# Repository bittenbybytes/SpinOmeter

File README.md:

# SpinOmeter
Spin gauge module for ultimate discs

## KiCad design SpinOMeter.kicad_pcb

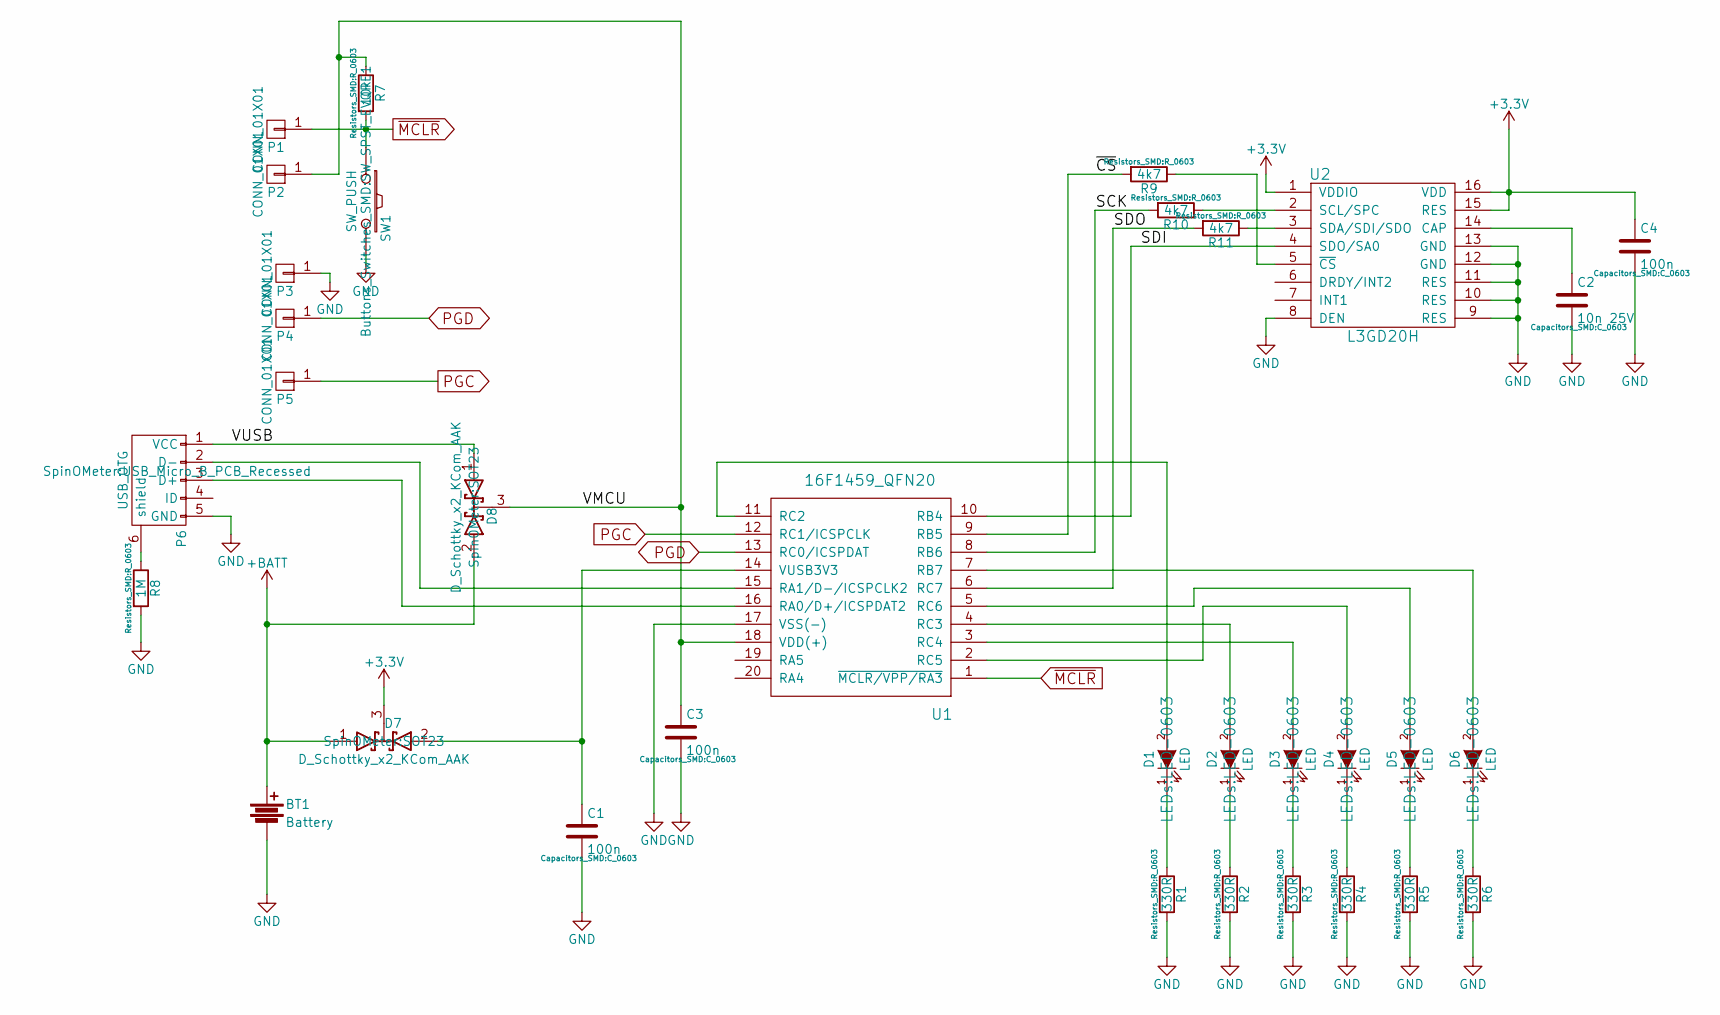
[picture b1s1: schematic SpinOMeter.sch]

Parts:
BT1: Battery; CR2032_Holder_THT
C1, C3, C4: 100n; C_0603
C2: 10n 25V; C_0603
D1, D2, D3, D4, D5, D6: LED; LED-0603
D7, D8: D_Schottky_x2_KCom_AAK; SOT23
P1, P2, P3, P4, P5: CONN_01X01; PINTST
P6: USB_OTG; USB_Micro_B_PCB_Recessed
R1, R2, R3, R4, R5, R6: 330R; R_0603
R7: 10k; R_0603
R8: 1M; R_0603
R9, R10, R11: 4k7; R_0603
SW1: SW_PUSH; SW_SPST_EVQPE1
U1: 16F1459_QFN20; QFN20_0.5mm_pitch
U2: L3GD20H; LGA16_3x3x1

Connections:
+3V3: C4.1, D7.3 (K), U2.1 (VDDIO), U2.15 (RES), U2.16 (VDD)
+BATT: BT1.1, D7.1 (A), D8.2 (A)
/SCK: R10.2, U1.8 (RB6)
/SDI: U1.10 (RB4), U2.4 (SDO/SA0)
/SDO: R11.2, U1.6 (RC7)
/VMCU: C3.1, D8.3 (K), P2.1, R7.1, U1.18 (VDD(+))
/VUSB: D8.1 (A), P6.1 (VCC)
/~CS~: R9.2, U1.9 (RB5)
GND: BT1.2, C1.2, C2.2, C3.2, C4.2, P3.1, P6.5 (GND), R1.2, R2.2, R3.2, R4.2, R5.2, R6.2, R8.2, SW1.2, U1.17 (VSS(-)), U2.8 (DEN), U2.9 (RES), U2.10 (RES), U2.11 (RES), U2.12 (GND), U2.13 (GND)
unnamed: C1.1, D7.2 (A), U1.14 (VUSB3V3)
unnamed: C2.1, U2.14 (CAP)
unnamed: D1.1 (K), R1.1
unnamed: D1.2 (A), U1.11 (RC2)
unnamed: D2.1 (K), R2.1
unnamed: D2.2 (A), U1.4 (RC3)
unnamed: D3.1 (K), R3.1
unnamed: D3.2 (A), U1.3 (RC4)
unnamed: D4.1 (K), R4.1
unnamed: D4.2 (A), U1.2 (RC5)
unnamed: D5.1 (K), R5.1
unnamed: D5.2 (A), U1.5 (RC6)
unnamed: D6.1 (K), R6.1
unnamed: D6.2 (A), U1.7 (RB7)
unnamed: P6.2 (D-), U1.15 (RA1/D-/ICSPCLK2)
unnamed: P6.3 (D+), U1.16 (RA0/D+/ICSPDAT2)
unnamed: P6.6 (shield), R8.1
unnamed: R9.1, U2.5 (~CS~)
unnamed: R10.1, U2.2 (SCL/SPC)
unnamed: R11.1, U2.3 (SDA/SDI/SDO)
PGC: P5.1, U1.12 (RC1/ICSPCLK)
PGD: P4.1, U1.13 (RC0/ICSPDAT)
~MCLR: P1.1, R7.2, SW1.1, U1.1 (~MCLR/VPP/RA3)

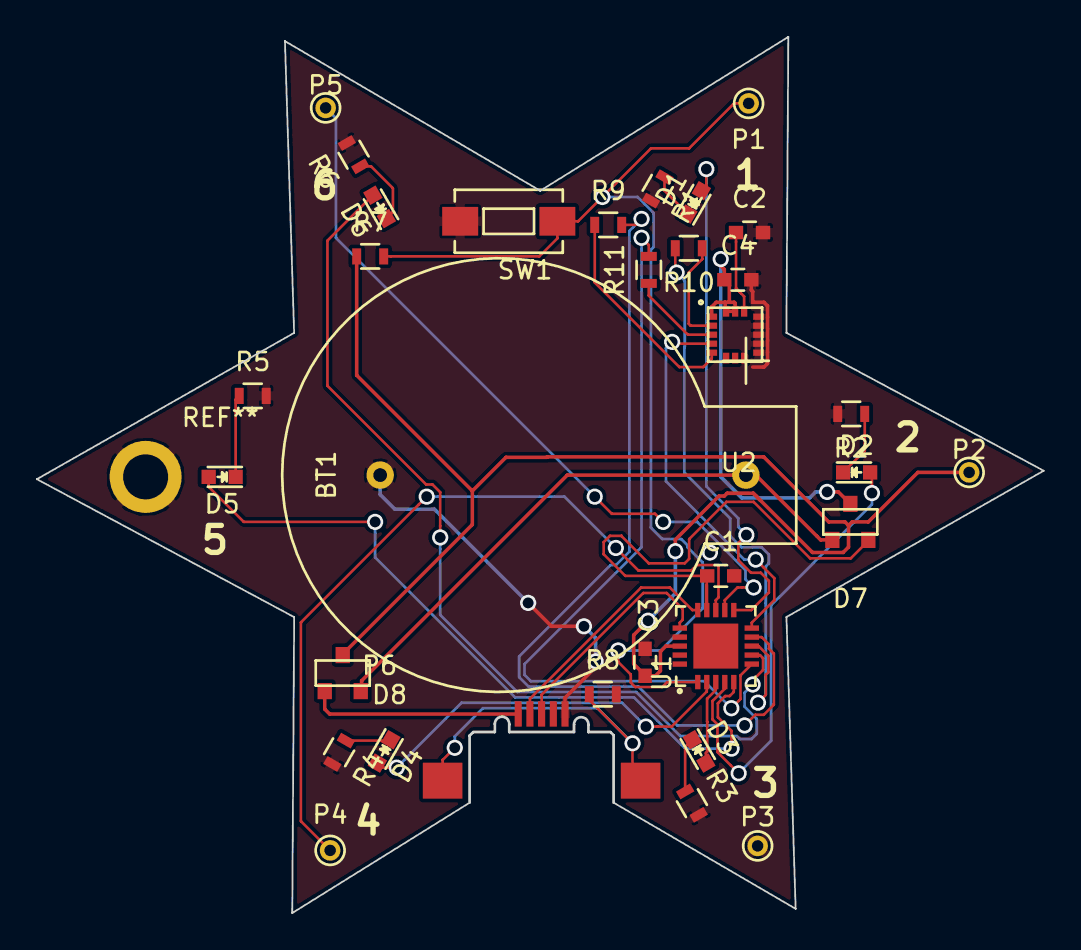
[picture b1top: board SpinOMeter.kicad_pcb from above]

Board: 2 copper layers, 55.9 x 48.6 mm, 33 parts (0 on the bottom side), 32 nets.

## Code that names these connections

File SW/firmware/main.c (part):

/*
    example minimal CDC serial port adapter using PIC16F1454 microcontroller

    this is specific to the PIC16F1454; TX is on pin RC4 and RX on pin RC5

    based on M-Stack by Alan Ott, Signal 11 Software

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	PORTC = 0X00;

	TRISBbits.TRISB7 = 0;
	PORTBbits.RB7 = 1;

	//InitializeUSART();
	initMilisTimer();
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	initGyro();

    TRISBbits.TRISB7 = 0;
	PORTBbits.RB7 = 1;
    
	PIC2PC_pending_count = 0;
	PC2PIC_buffer_occupancy = 0;
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#define SCL LATBbits.LATB6
#define SCL_TRIS TRISBbits.TRISB6

#define SDO LATCbits.LATC7
#define SDO_TRIS TRISCbits.TRISC7

#define SDI PORTBbits.RB4
#define SDI_TRIS TRISBbits.TRISB4

void initSPI()
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
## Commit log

2016-11-09 Created repository for project
2016-11-10 Added missing Makefile
2016-11-26 Fixed pin mixup. Created Low Power project without USB
2016-11-26 added Makefile

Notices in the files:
SW/firmware/main.c:
Copyright (C) 2014,2015 Peter Lawrence
